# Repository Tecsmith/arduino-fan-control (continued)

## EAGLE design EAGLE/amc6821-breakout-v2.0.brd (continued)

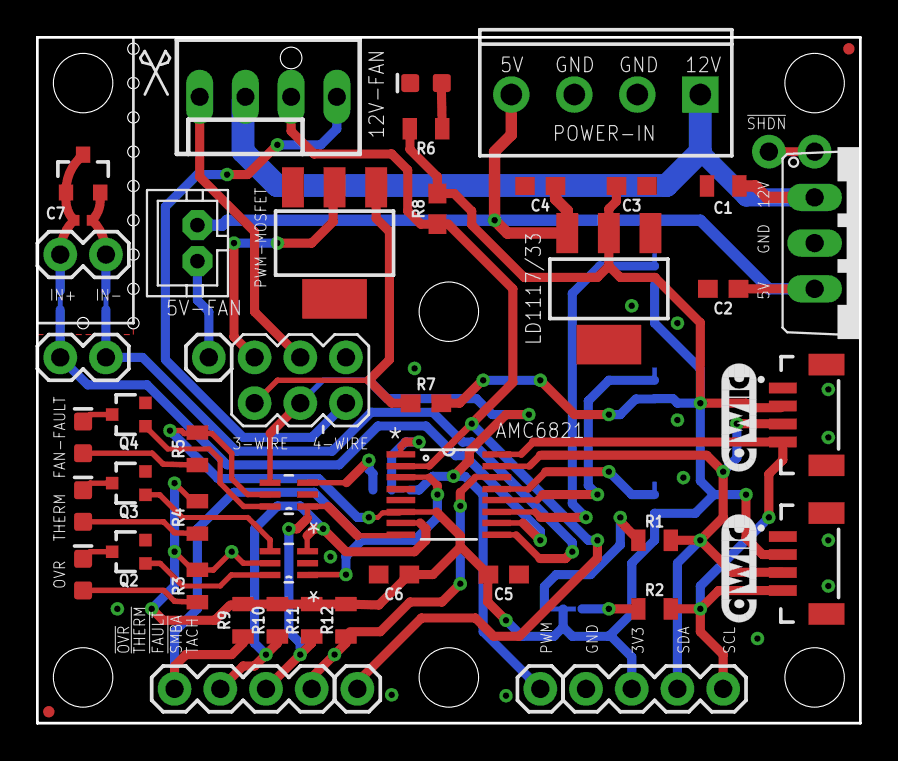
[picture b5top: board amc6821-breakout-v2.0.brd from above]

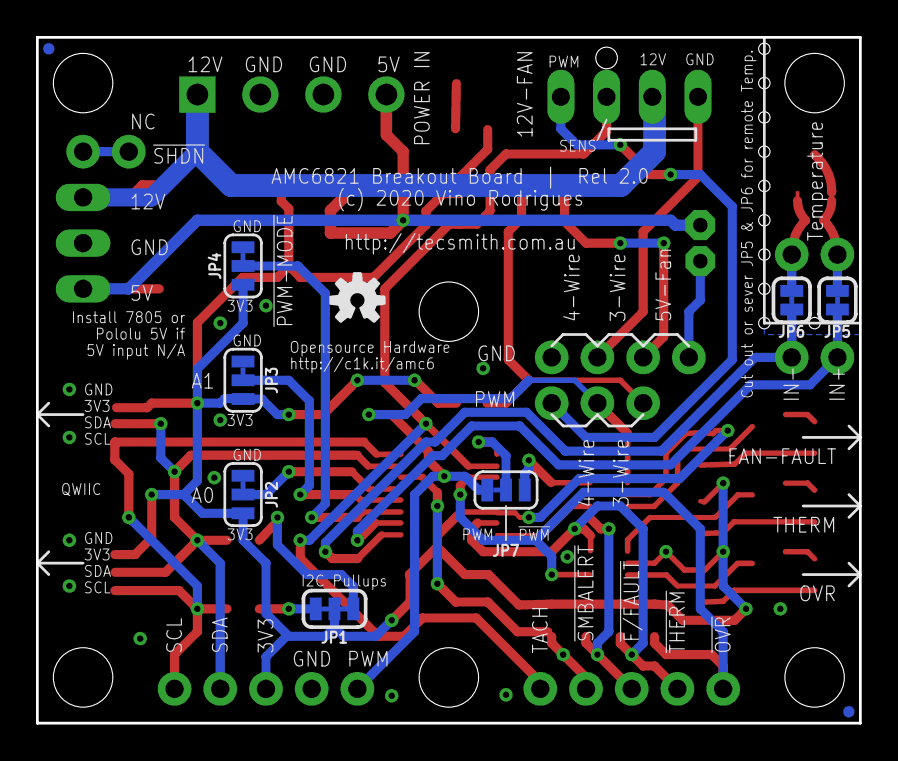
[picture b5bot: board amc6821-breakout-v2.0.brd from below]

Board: 2 copper layers, 45.7 x 38.1 mm, 67 parts (11 on the bottom side), 39 nets.

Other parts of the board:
LOGO5: QWIIC_LOGO_6MM; QWIIC_6MM

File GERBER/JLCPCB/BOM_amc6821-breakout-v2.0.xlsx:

Comment | Designator | Footprint | LCSC Part #（optional） | LCSC Type | Farnell Part #
0.1uF (100nF) | C2, C6 | 805 | C49678 | Basic
0.33µF (330nF) | C1 | 805 | C1740 | Basic
1.0nF | C7 | 805 | C46653 | Basic
10uF | C3, C4, C5 | 805 | C15850 | Basic
RED | D1, D2, D3 | LED_0805 | C84256 | Basic
GREEN | D4 | LED-0805 | C205442 | Basic
2N3904 | Q1 | SOT-23-3 | C20526 | Basic
2N7002 | Q2,Q3,Q4 | SOT-23-3 | C8545 | Basic
3.3K | R1, R2, R9, R10, R11, R12 | 805 | C26010 | Basic
1.5k | R7 | 805 | C17630 | Basic
300 | R3, R4, R5, R6 | 805 | C17617 | Basic
10k | R8 | 805 | C17414 | Basic
LD1117-33 | U4 | SOT-223 | C6186 | Basic
NDT3055L | Q5 | SOT-223-3 | C725128 | Extended
AMC6821-Q1QSOP-16N | U1 | SSOP-16_3.9x4.9x0.635P | C555157 | Extended
SN74LVC2G14DCKR | U2, U3 | SOT-363 | C37361 | Extended
J4 | J4 | SCREWTERMINAL-3.5MM-4 | --- | --- | 247858802
JST-PH-2 | 5V-FAN | JST-PH2 | --- | --- | 9491856
KK-254-4KK-254 | J5 | MOLEX_47053-1000 | --- | --- | 2313705
Qwiic | J1, J2 | JST04_1MM_VERT | --- | --- | 1830839

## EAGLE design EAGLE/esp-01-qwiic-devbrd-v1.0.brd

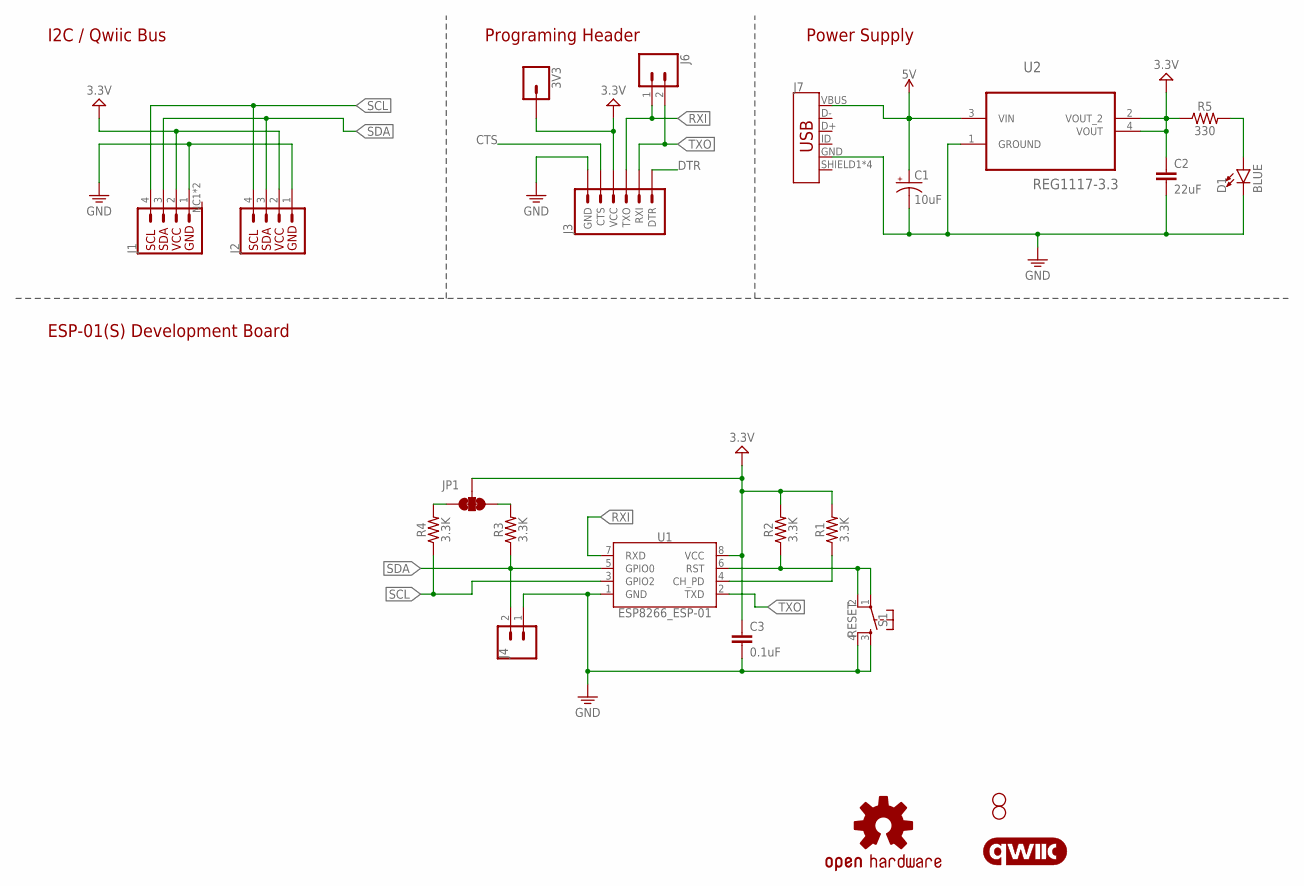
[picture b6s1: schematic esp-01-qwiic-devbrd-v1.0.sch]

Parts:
3V3: CONN_01PTH_NO_SILK_YES_STOP; 1X01_NO_SILK
C1: 10uF; EIA3216
C2: 22uF; 0805
C3: 0.1uF; 0603
D1: BLUE; LED-0603
H1, H2: STAND-OFF
J1: QWIIC_CONNECTORJST04_1MM_RA_GND; JST04_1MM_RA
J2: I2C_STANDARD; 1X04
J3: 6_PIN_SERIAL_TARGETSILK; 6_PIN_SERIAL_TARGET_SIDE_W_SILK
J4: CONN_02; 1X02
J6: CONN_021X02_NO_SILK; 1X02_NO_SILK
J7: USB_MICRO-B_FEMALE-SMT; USB-B-MICRO-SMD
JP1: JUMPER-SMT_3_2-NC_TRACE_SILK; SMT-JUMPER_3_2-NC_TRACE_SILK
LOGO1: OSHW-LOGOS; OSHW-LOGO-S
LOGO2: QWIIC_LOGO_6MM; QWIIC_6MM
R1, R2, R3, R4: 3.3K; 0805
R5: 330; 0603
S1: RESET; TACTILE_SWITCH_SMD_5.2MM
U1: ESP8266_ESP-01
U2: REG1117-3.3; SOT230P700X180-4N

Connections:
5V: C1.+, J7.VBUS, U2.3 (VIN)
CTS: J3.5 (CTS)
DTR: J3.1 (DTR)
GND: C1.-, C2.2, C3.2, D1.C, J1.1, J2.1, J3.6 (GND), J4.1, J7.GND, S1.3, S1.4, U1.1 (GND), U2.1 (GROUND)
unnamed: R2.1, S1.1, S1.2, U1.6 (RST)
unnamed: D1.A, R5.2
unnamed: R1.1, U1.4 (CH_PD)
unnamed: JP1.3, R4.2
unnamed: JP1.1, R3.2
RXI: J3.2 (TXO), J6.1, U1.7 (RXD)
SCL: J1.4, J2.4, R4.1, U1.3 (GPIO2)
SDA: J1.3, J2.3, J4.2, R3.1, U1.5 (GPIO0)
TXO: J3.3 (RXI), J6.2, U1.2 (TXD)
VCC: 3V3.1, C2.1, C3.1, J1.2, J2.2, J3.4 (VCC), JP1.2, R1.2, R2.2, R5.1, U1.8 (VCC), U2.2 (VOUT_2), U2.4 (VOUT)

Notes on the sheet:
I2C / Qwiic Bus
Programing Header
Power Supply
ESP-01(S) Development Board

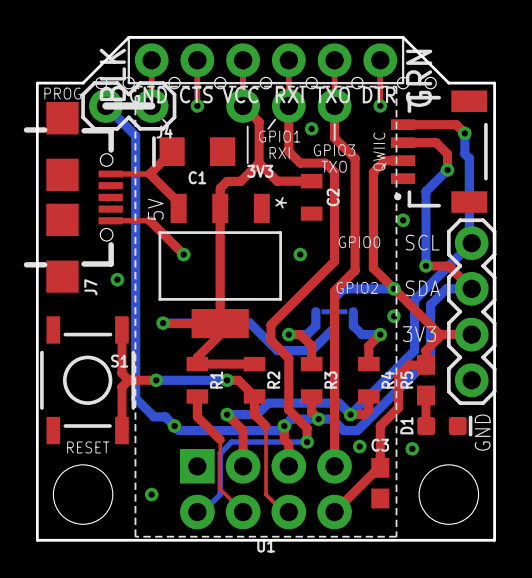
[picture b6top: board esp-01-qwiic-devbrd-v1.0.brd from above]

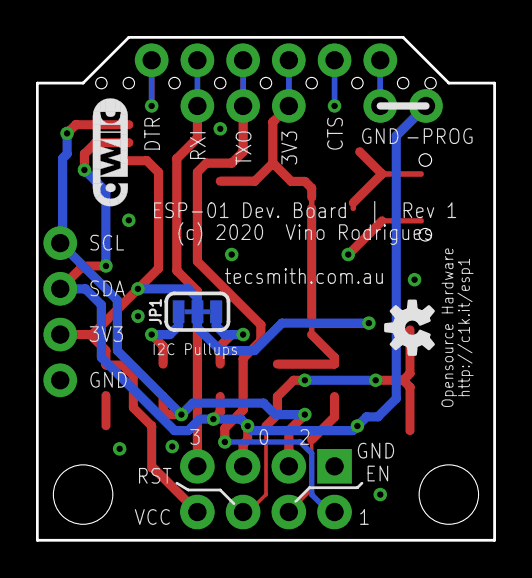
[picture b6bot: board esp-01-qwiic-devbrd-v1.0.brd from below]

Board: 2 copper layers, 25.4 x 27.9 mm, 24 parts (3 on the bottom side), 12 nets.

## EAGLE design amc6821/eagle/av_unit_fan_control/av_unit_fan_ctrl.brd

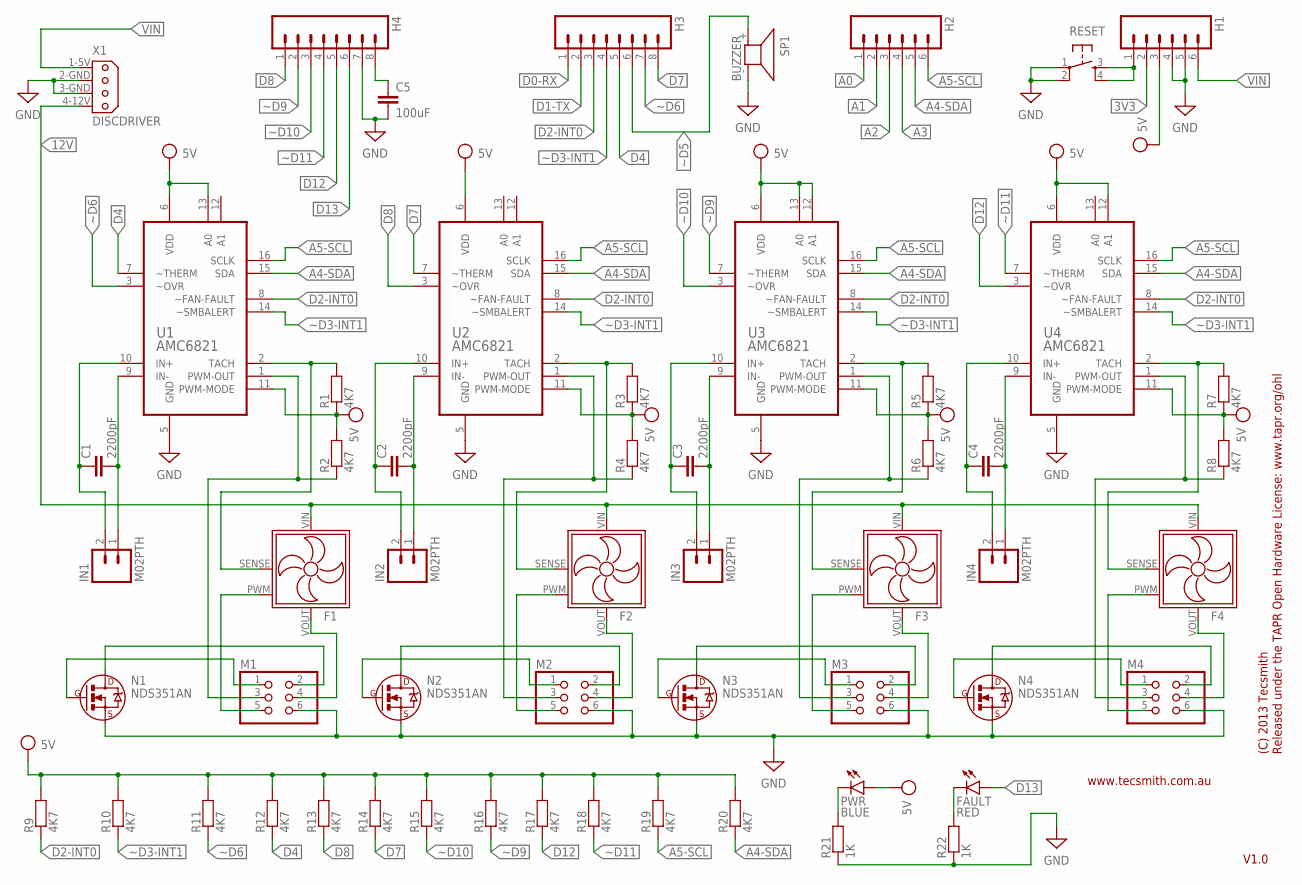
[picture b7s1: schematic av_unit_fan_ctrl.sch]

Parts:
C1, C2, C3, C4: 2200pF; 0603
C5: 100uF; 0603
F1, F2, F3, F4: FAN_4-WIREINTEL; 47053-1000
FAULT: RED; LED-0603
H1, H2: M06SIP; 1X06
H3, H4: M08; 1X08
IN1, IN2, IN3, IN4: M02PTH; 1X02
M1, M2, M3, M4: PINHD-2X3; 2X03
N1, N2, N3, N4: NDS351AN; SOT23
PWR: BLUE; LED-0603
R1, R2, R3, R4, R5, R6, R7, R8, R9, R10, R11, R12, R13, R14, R15, R16, R17, R18, R19, R20: 4K7; 0603
R21, R22: 1K; 0603
RESET: TAC_SWITCHPTH; TACTILE-PTH
SP1: BUZZER; KSTG951AP
U1, U2, U3, U4: AMC6821; QSOP-16N
X1: DISCDRIVER; 9090-4R

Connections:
3V3: H1.2
5V: H1.3, PWR.A, R1.1, R2.2, R3.1, R4.2, R5.1, R6.2, R7.1, R8.2, R9.2, R10.2, R11.2, R12.2, R13.2, R14.2, R15.2, R16.2, R17.2, R18.2, R19.2, R20.2, U1.6 (VDD), U1.11 (PWM-MODE), U1.13 (A0), U2.6 (VDD), U2.11 (PWM-MODE), U3.6 (VDD), U3.11 (PWM-MODE), U3.12 (A1), U3.13 (A0), U4.6 (VDD), U4.11 (PWM-MODE), U4.12 (A1)
12V: F1.VIN (PWR), F2.VIN (PWR), F3.VIN (PWR), F4.VIN (PWR), X1.4-12V
A0: H2.1
A1: H2.2
A2: H2.3
A3: H2.4
A4-SDA: H2.5, R20.1, U1.15 (SDA), U2.15 (SDA), U3.15 (SDA)
A5-SCL: H2.6, R19.1, U1.16 (SCLK), U2.16 (SCLK), U3.16 (SCLK), U4.16 (SCLK)
AREF: C5.1, H4.8
D0-RX: H3.1
D1-TX: H3.2
D2-INT0: H3.3, R9.1, U1.8 (~FAN-FAULT), U2.8 (~FAN-FAULT), U3.8 (~FAN-FAULT), U4.8 (~FAN-FAULT)
D4: H3.5, R12.1, U1.7 (~THERM)
D7: H3.8, R14.1, U2.7 (~THERM)
D8: H4.1, R13.1, U2.3 (~OVR)
D12: H4.5, R17.1, U4.3 (~OVR)
D13: FAULT.A, H4.6
GND: C5.2, H1.4, H1.5, H4.7, M1.6, M2.6, M3.6, M4.6, N1.2 (S), N2.2 (S), N3.2 (S), N4.2 (S), R21.1, R22.1, RESET.1, RESET.2, SP1.- (2), U1.5 (GND), U2.5 (GND), U3.5 (GND), U4.5 (GND), X1.2-GND, X1.3-GND
unnamed: F1.VOUT (GND), M1.4
unnamed: F2.VOUT (GND), M2.4
unnamed: F1.PWM, M1.5
unnamed: F4.VOUT (GND), M4.4
unnamed: M1.2, N1.3 (D)
unnamed: M2.2, N2.3 (D)
unnamed: M3.2, N3.3 (D)
unnamed: M4.2, N4.3 (D)
unnamed: FAULT.C, R22.2
unnamed: PWR.C, R21.2
unnamed: M1.1, N1.1 (G)
unnamed: M4.3, R8.1, U4.1 (PWM-OUT)
unnamed: M3.1, N3.1 (G)
unnamed: F4.SENSE, R7.2, U4.2 (TACH)
unnamed: M3.3, R6.1, U3.1 (PWM-OUT)
unnamed: F3.SENSE, R5.2, U3.2 (TACH)
unnamed: C1.1, IN1.2, U1.10 (IN+)
unnamed: M2.3, R4.1, U2.1 (PWM-OUT)
unnamed: F2.SENSE, R3.2, U2.2 (TACH)
unnamed: M2.1, N2.1 (G)
unnamed: H1.1, RESET.3, RESET.4
unnamed: F4.PWM, M4.5
unnamed: F3.PWM, M3.5
unnamed: M4.1, N4.1 (G)
unnamed: M1.3, R2.1, U1.1 (PWM-OUT)
unnamed: F1.SENSE, R1.2, U1.2 (TACH)
unnamed: F3.VOUT (GND), M3.4
unnamed: F2.PWM, M2.5
unnamed: C4.1, IN4.2, U4.10 (IN+)
unnamed: C3.1, IN3.2, U3.10 (IN+)
unnamed: C2.1, IN2.2, U2.10 (IN+)
unnamed: C1.2, IN1.1, U1.9 (IN-)
unnamed: C2.2, IN2.1, U2.9 (IN-)
unnamed: C3.2, IN3.1, U3.9 (IN-)
unnamed: C4.2, IN4.1, U4.9 (IN-)
VIN: H1.6, X1.1-5V
~D3-INT1: H3.4, R10.1, U1.14 (~SMBALERT), U2.14 (~SMBALERT), U3.14 (~SMBALERT), U4.14 (~SMBALERT)
~D5: H3.6, SP1.+ (1)
~D6: H3.7, R11.1, U1.3 (~OVR)
~D9: H4.2, R16.1, U3.7 (~THERM)
~D10: H4.3, R15.1, U3.3 (~OVR)
~D11: H4.4, R18.1, U4.7 (~THERM)

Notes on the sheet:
V1.0
(C) 2013 Tecsmith
Released under the TAPR Open Hardware License: www.tapr.org/ohl
www.tecsmith.com.au

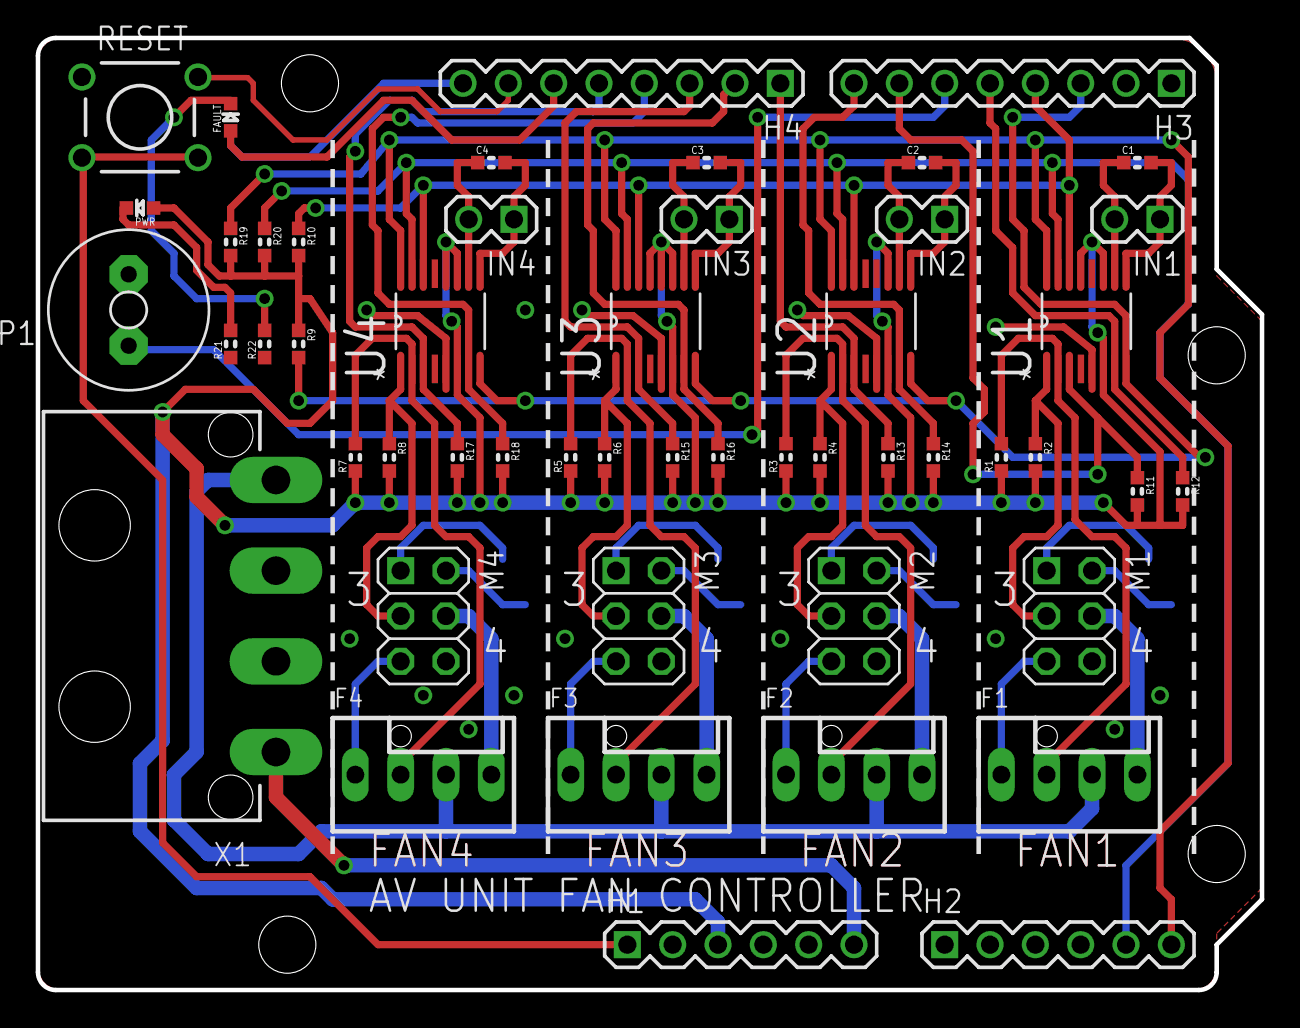
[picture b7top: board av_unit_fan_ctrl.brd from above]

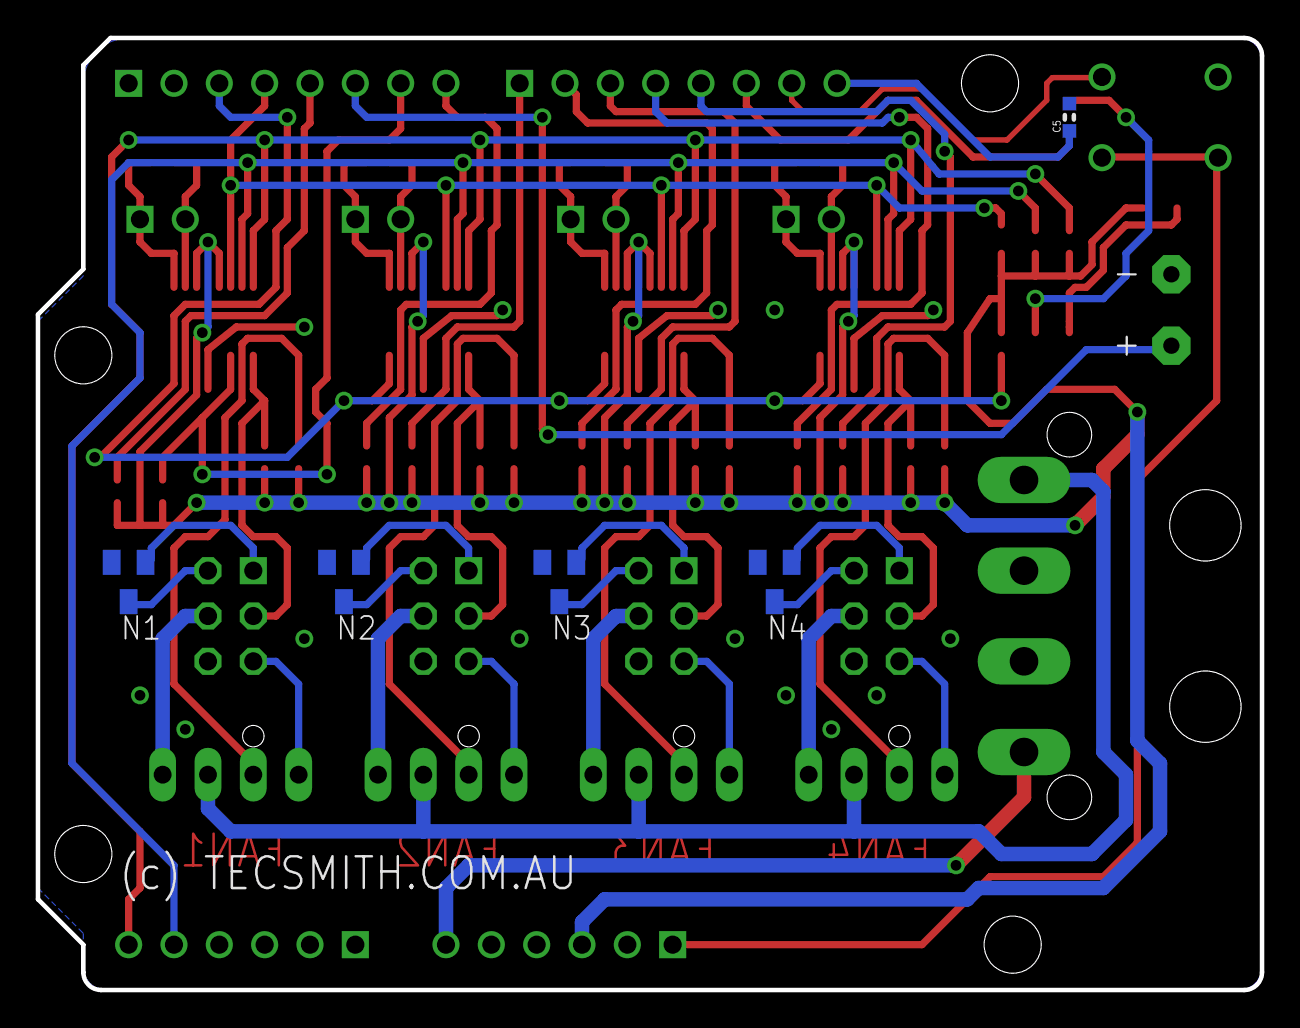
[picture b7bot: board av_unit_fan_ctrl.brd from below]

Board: 2 copper layers, 68.6 x 53.3 mm, 56 parts (5 on the bottom side), 54 nets.

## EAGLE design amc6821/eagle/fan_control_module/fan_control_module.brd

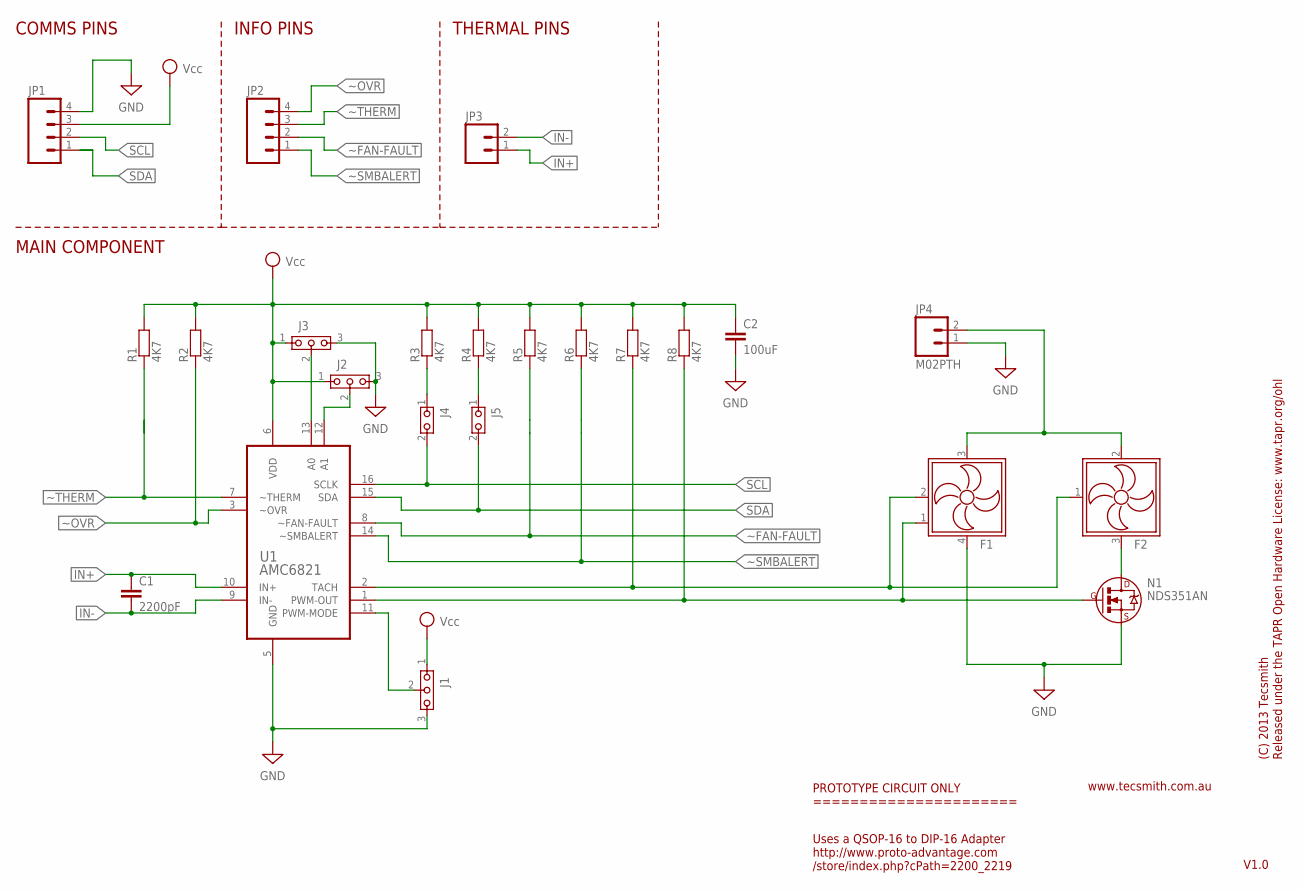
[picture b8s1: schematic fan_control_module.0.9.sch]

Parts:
C1: 2200pF; 0603
C2: 100uF; 0603
F1: FAN_4-WIREINTEL; 47053-1000
F2: FAN_3-WIRE; 22-23-2031
J1, J2, J3: SJ3SMD; SJ2
J4, J5: SJSMD; SJ
JP1, JP2: M04PTH; 1X04
JP3, JP4: M02PTH; 1X02
N1: NDS351AN; SOT23
R1, R2, R3, R4, R5, R6, R7, R8: 4K7; 0603
U1: AMC6821; QSOP-16N

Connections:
3WIRE-GND: F2.3 (GND), N1.3 (D)
A0: J3.2, U1.13 (A0)
A1: J2.2, U1.12 (A1)
GND: C2.2, F1.4 (GND), J1.3, J2.3, J3.3, JP1.4, JP4.1, N1.2 (S), U1.5 (GND)
IN+: C1.1, JP3.1, U1.10 (IN+)
IN-: C1.2, JP3.2, U1.9 (IN-)
PWM: F1.1 (PWM), N1.1 (G), R8.1, U1.1 (PWM-OUT)
PWM-MODE: J1.2, U1.11 (PWM-MODE)
SCL: J4.2, JP1.2, U1.16 (SCLK)
SCL-X: J4.1, R3.1
SDA: J5.2, JP1.1, U1.15 (SDA)
SDA-X: J5.1, R4.1
TACH: F1.2 (SENSE), F2.1 (SENSE), R7.1, U1.2 (TACH)
VCC: C2.1, J1.1, J2.1, J3.1, JP1.3, R1.2, R2.2, R3.2, R4.2, R5.2, R6.2, R7.2, R8.2, U1.6 (VDD)
VFAN: F1.3 (PWR), F2.2 (PWR), JP4.2
~FAN-FAULT: JP2.2, R5.1, U1.8 (~FAN-FAULT)
~OVR: JP2.4, R2.1, U1.3 (~OVR)
~SMBALERT: JP2.1, R6.1, U1.14 (~SMBALERT)
~THERM: JP2.3, R1.1, U1.7 (~THERM)

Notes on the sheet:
V1.0
(C) 2013 Tecsmith
Released under the TAPR Open Hardware License: www.tapr.org/ohl
www.tecsmith.com.au
PROTOTYPE CIRCUIT ONLY ======================
Uses a QSOP-16 to DIP-16 Adapter http://www.proto-advantage.com /store/index.php?cPath=2200_2219
COMMS PINS
INFO PINS
THERMAL PINS
MAIN COMPONENT

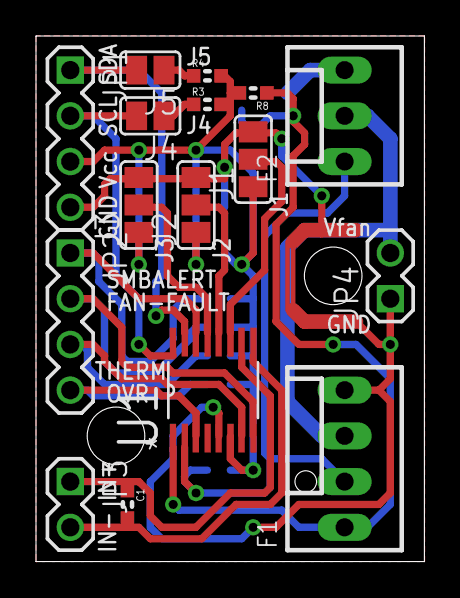
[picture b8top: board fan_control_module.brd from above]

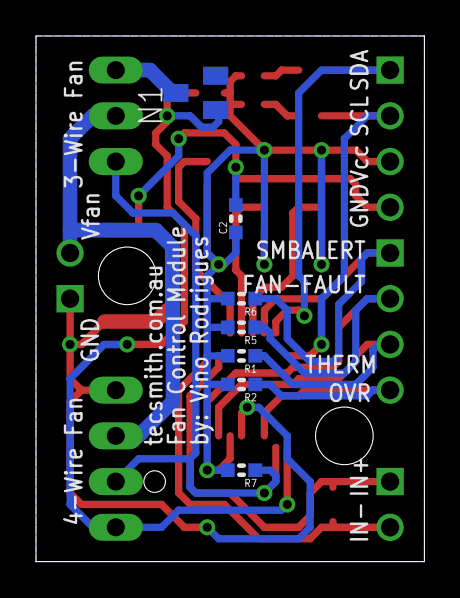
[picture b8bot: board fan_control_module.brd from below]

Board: 2 copper layers, 21.6 x 29.2 mm, 23 parts (7 on the bottom side), 19 nets.

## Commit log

2013-06-04 initial
2013-06-04 initial upload
2013-06-04 whoop, whoop, whoop
2013-09-08 rename
2016-04-05 readme.md file
2019-04-05 Deprecated
2021-07-11 re-upload of v2.0
2021-07-11 re-upload of v2.3
2021-07-11 clean up of v2.3
2021-07-12 remove v2.3 files
2021-07-18 v3 upload - split into 2 boards
2021-07-18 Upload of simple docs
2021-07-19 copy of Mark Burke's white-paper
2021-07-19 fixes to the TACH lines
2021-07-19 move C3 closer to the IC
2021-07-19 update to the docs
2021-07-19 minor rename, JP4
2021-07-20 minor edits
2021-09-16 added more vendor specs
2021-09-18 rounded corners
2021-09-24 added LED interface
2021-10-12 added active buzzer
